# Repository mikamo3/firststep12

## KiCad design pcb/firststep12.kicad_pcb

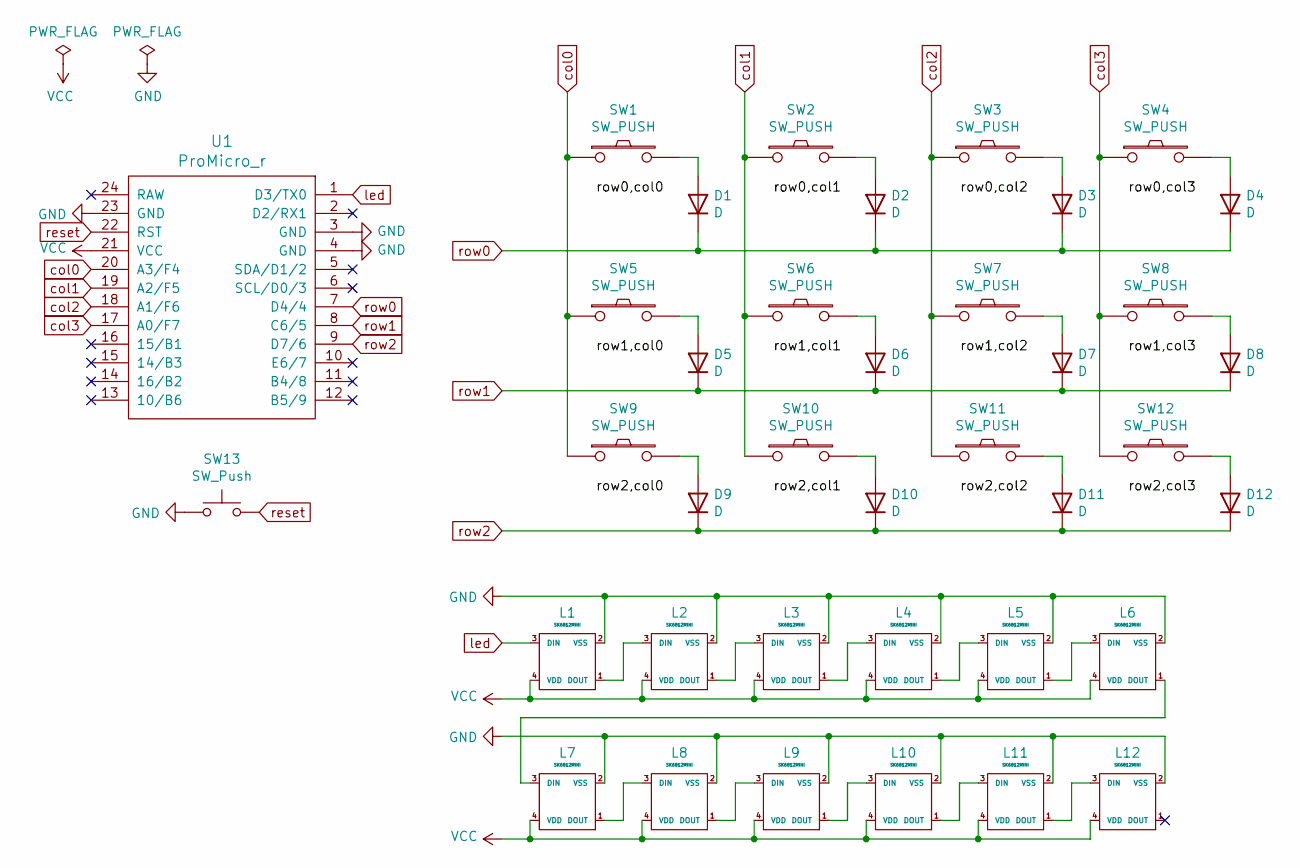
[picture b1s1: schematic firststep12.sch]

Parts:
D1, D2, D3, D4, D5, D6, D7, D8, D9, D10, D11, D12: D; D3_TH
L1, L2, L3, L4, L5, L6, L7, L8, L9, L10, L11, L12: SK6812MINI; SK6812MINI_rev
SW1, SW2, SW3, SW4, SW5, SW6, SW7, SW8, SW9, SW10, SW11, SW12: SW_PUSH; CherryMX_1u
SW13: SW_Push; ResetSW_1side
U1: ProMicro_r; ProMicro_v3.5

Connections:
GND: L1.2 (VSS), L2.2 (VSS), L3.2 (VSS), L4.2 (VSS), L5.2 (VSS), L6.2 (VSS), L7.2 (VSS), L8.2 (VSS), L9.2 (VSS), L10.2 (VSS), L11.2 (VSS), L12.2 (VSS), SW13.1, U1.3 (GND), U1.4 (GND), U1.23 (GND)
unnamed: D1.2 (A), SW1.2
unnamed: D2.2 (A), SW2.2
unnamed: D3.2 (A), SW3.2
unnamed: D4.2 (A), SW4.2
unnamed: D5.2 (A), SW5.2
unnamed: D6.2 (A), SW6.2
unnamed: D7.2 (A), SW7.2
unnamed: D8.2 (A), SW8.2
unnamed: D9.2 (A), SW9.2
unnamed: D10.2 (A), SW10.2
unnamed: D11.2 (A), SW11.2
unnamed: D12.2 (A), SW12.2
unnamed: L1.1 (DOUT), L2.3 (DIN)
unnamed: L2.1 (DOUT), L3.3 (DIN)
unnamed: L3.1 (DOUT), L4.3 (DIN)
unnamed: L4.1 (DOUT), L5.3 (DIN)
unnamed: L5.1 (DOUT), L6.3 (DIN)
unnamed: L6.1 (DOUT), L7.3 (DIN)
unnamed: L7.1 (DOUT), L8.3 (DIN)
unnamed: L8.1 (DOUT), L9.3 (DIN)
unnamed: L10.1 (DOUT), L11.3 (DIN)
unnamed: L9.1 (DOUT), L10.3 (DIN)
unnamed: L11.1 (DOUT), L12.3 (DIN)
VCC: L1.4 (VDD), L2.4 (VDD), L3.4 (VDD), L4.4 (VDD), L5.4 (VDD), L6.4 (VDD), L7.4 (VDD), L8.4 (VDD), L9.4 (VDD), L10.4 (VDD), L11.4 (VDD), L12.4 (VDD), U1.21 (VCC)
col0: SW1.1, SW5.1, SW9.1, U1.20 (A3/F4)
col1: SW2.1, SW6.1, SW10.1, U1.19 (A2/F5)
col2: SW3.1, SW7.1, SW11.1, U1.18 (A1/F6)
col3: SW4.1, SW8.1, SW12.1, U1.17 (A0/F7)
led: L1.3 (DIN), U1.1 (D3/TX0)
reset: SW13.2, U1.22 (RST)
row0: D1.1 (K), D2.1 (K), D3.1 (K), D4.1 (K), U1.7 (D4/4)
row1: D5.1 (K), D6.1 (K), D7.1 (K), D8.1 (K), U1.8 (C6/5)
row2: D9.1 (K), D10.1 (K), D11.1 (K), D12.1 (K), U1.9 (D7/6)

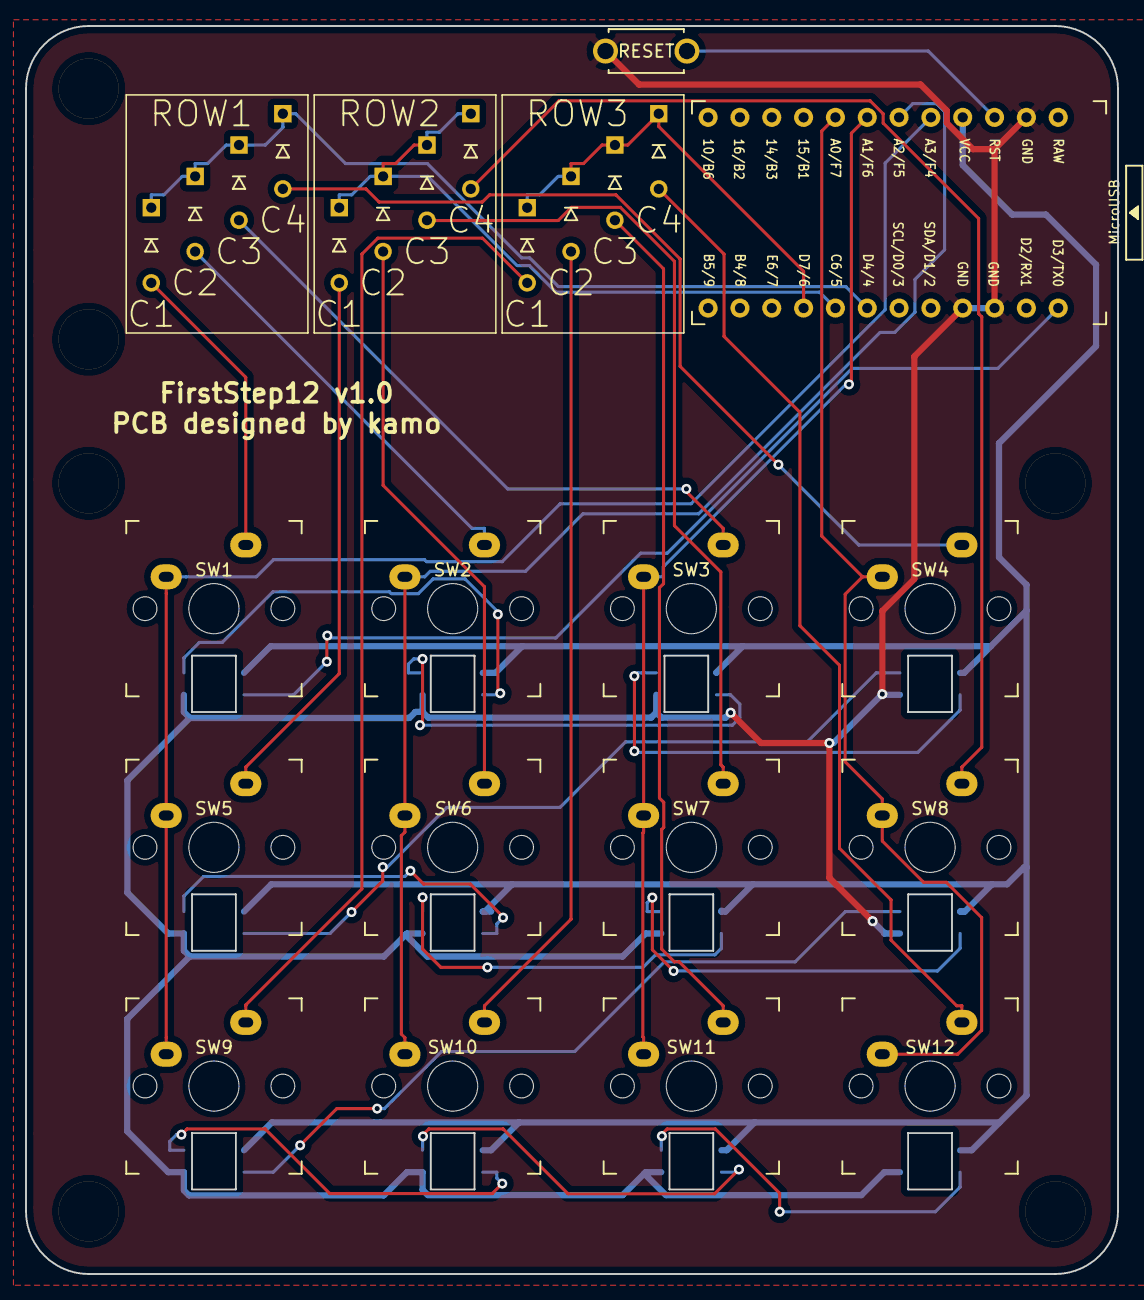
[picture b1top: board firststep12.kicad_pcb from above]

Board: 2 copper layers, 87.2 x 99.6 mm, 44 parts (0 on the bottom side), 34 nets.

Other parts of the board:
H1, H2, H3, H4, H5, H6: M2_HOLE_v2

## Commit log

2020-06-13 create project
2020-06-13 create schema
2020-06-13 create netlist
2020-06-21 create pcb
2020-06-25 add compress script
2020-06-25 add gerber, bottom plate, top plate
2020-11-07 add keyboad layout
